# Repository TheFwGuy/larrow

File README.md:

Larrow project with Energia

To compile, Set Energia to have the library included and open larrow.ino.
This directory should be placed in the main directory where the sketches are
kept.

It is necessary to have these libraries installed in the library directory:

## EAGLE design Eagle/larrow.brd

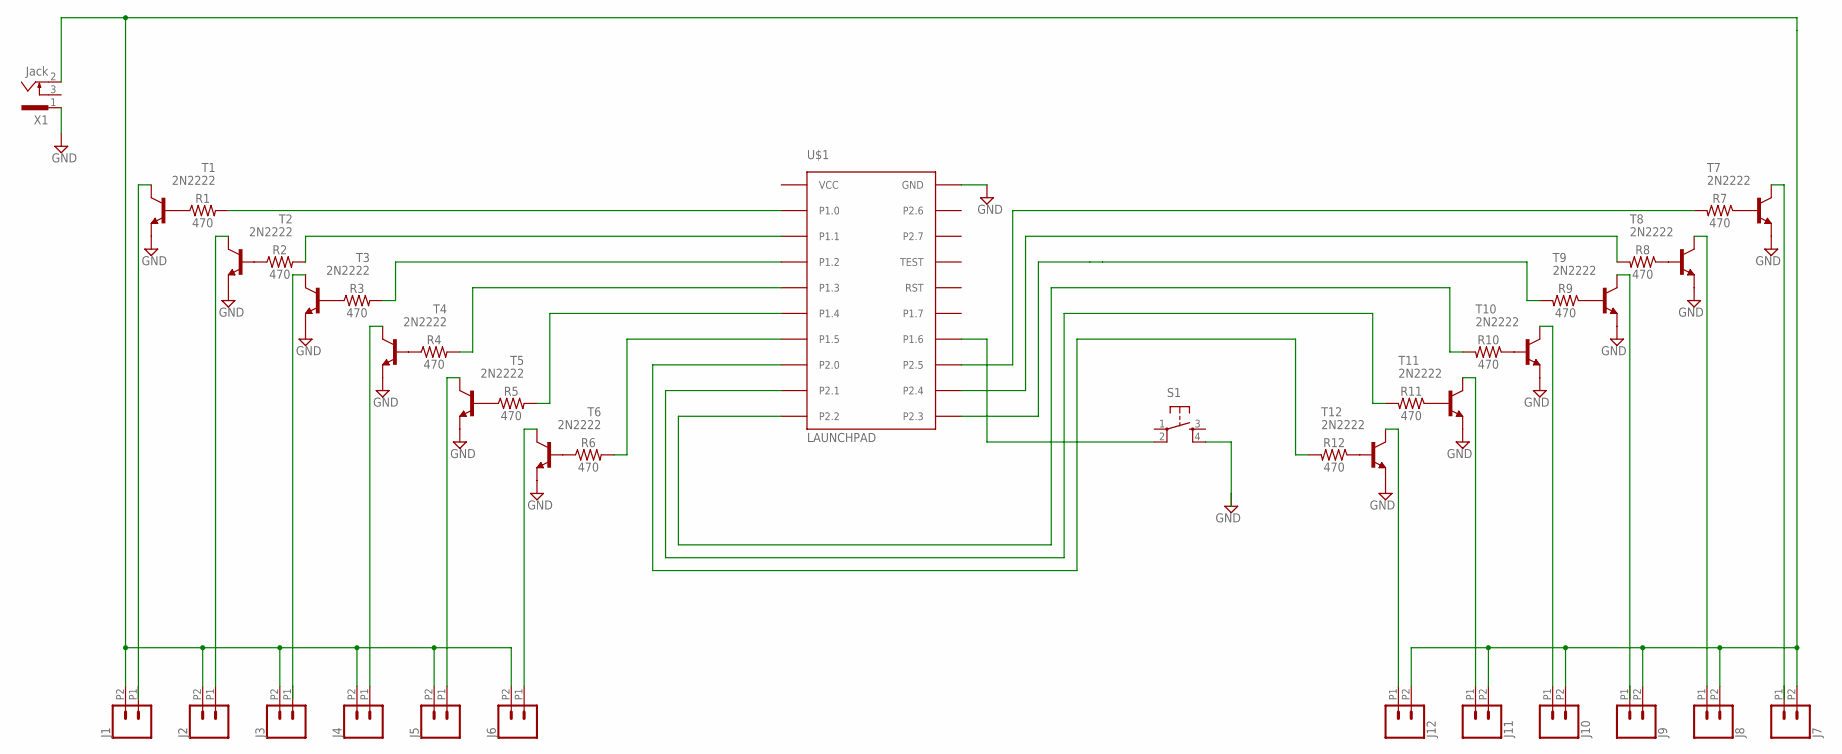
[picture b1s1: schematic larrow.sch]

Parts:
J1, J2, J3, J4, J5, J6, J7, J8, J9, J10, J11, J12: CONN_022.54MM_SCREWTERM; 1X02_2.54_SCREWTERM
R1, R2, R3, R4, R5, R6, R7, R8, R9, R10, R11, R12: 470; AXIAL-0.3
S1: TAC_SWITCHPTH; TACTILE-PTH
T1, T2, T3, T4, T5, T6, T7, T8, T9, T10, T11, T12: 2N2222; TO92-EBC-OVAL
U$1: LAUNCHPAD
X1: Jack; SCD-014-A

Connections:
GND: S1.4, T1.E, T2.E, T3.E, T4.E, T5.E, T6.E, T7.E, T8.E, T9.E, T10.E, T11.E, T12.E, U$1.GND, X1.1
unnamed: J2.P1 (1), T2.C
unnamed: J1.P1 (1), T1.C
unnamed: R2.P$1 (1), T2.B
unnamed: R1.P$1 (1), T1.B
unnamed: R1.P$2 (2), U$1.P1.0
unnamed: R3.P$1 (1), T3.B
unnamed: J3.P1 (1), T3.C
unnamed: R4.P$1 (1), T4.B
unnamed: J4.P1 (1), T4.C
unnamed: R2.P$2 (2), U$1.P1.1
unnamed: R3.P$2 (2), U$1.P1.2
unnamed: R4.P$2 (2), U$1.P1.3
unnamed: R5.P$1 (1), T5.B
unnamed: J5.P1 (1), T5.C
unnamed: R5.P$2 (2), U$1.P1.4
unnamed: R6.P$1 (1), T6.B
unnamed: J6.P1 (1), T6.C
unnamed: R6.P$2 (2), U$1.P1.5
unnamed: R7.P$1 (1), T7.B
unnamed: J1.P2 (2), J2.P2 (2), J3.P2 (2), J4.P2 (2), J5.P2 (2), J6.P2 (2), J7.P2 (2), J8.P2 (2), J9.P2 (2), J10.P2 (2), J11.P2 (2), J12.P2 (2), X1.2
unnamed: J7.P1 (1), T7.C
unnamed: R8.P$1 (1), T8.B
unnamed: J8.P1 (1), T8.C
unnamed: R9.P$1 (1), T9.B
unnamed: J9.P1 (1), T9.C
unnamed: R10.P$1 (1), T10.B
unnamed: J10.P1 (1), T10.C
unnamed: R8.P$2 (2), U$1.P2.4
unnamed: R9.P$2 (2), U$1.P2.3
unnamed: R10.P$2 (2), U$1.P2.2
unnamed: R11.P$1 (1), T11.B
unnamed: J11.P1 (1), T11.C
unnamed: R11.P$2 (2), U$1.P2.1
unnamed: R12.P$1 (1), T12.B
unnamed: J12.P1 (1), T12.C
unnamed: R12.P$2 (2), U$1.P2.0
unnamed: R7.P$2 (2), U$1.P2.5
unnamed: S1.2, U$1.P1.6
VCC: U$1.VCC

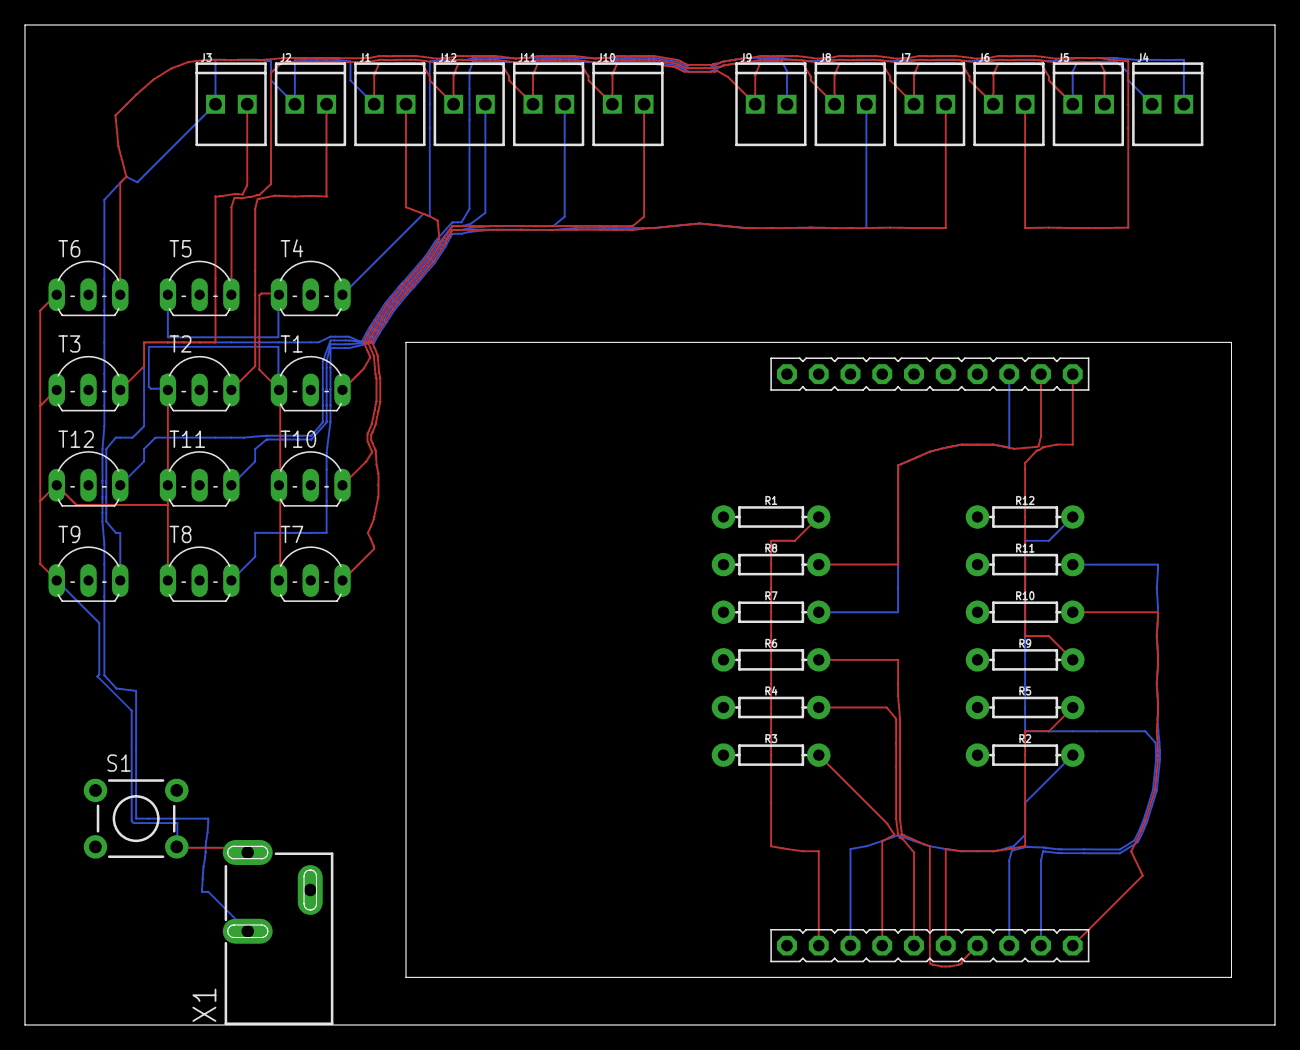
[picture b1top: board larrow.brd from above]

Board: 2 copper layers, 100.0 x 80.0 mm, 39 parts (0 on the bottom side), 39 nets.

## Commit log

2017-09-22 Removed temporary files
2017-09-22 Added label
2017-11-10 Revision during building
2018-05-18 New file Larrow.ino

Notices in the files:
parts and their libraries:
SparkFun-Connectors: Licensing: Creative Commons ShareAlike 4.0 International - https://creativecommons.org/licenses/by-sa/4.0
